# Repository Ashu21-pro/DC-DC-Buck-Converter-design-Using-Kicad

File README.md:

# Buck Converter PCB Design Using KiCad

## Overview

This project is a custom PCB design for a **DC-DC buck converter** that steps down a higher DC input voltage to a regulated **5 V output**. The design was created in KiCad, from the circuit schematic through PCB layout and 3D visualization.

The circuit uses an **LM2576HVS-5** fixed 5 V buck regulator, along with an inductor, Schottky diode, input/output capacitors, and an output indicator LED.

> **Note:** The schematic and PCB screenshots document the design process. Confirm the regulator's datasheet requirements, component ratings, footprint pin mapping, and PCB clearances before manufacturing or powering the board.

## Project Features

- Custom schematic capture in KiCad.
- Single-sided top-layer routing shown in the PCB layout.
- Screw-terminal connectors for DC input and 5 V output.
- Input and output filtering capacitors.
- Inductor and Schottky freewheeling diode for the buck-converter power stage.
- LED output indicator with a series current-limiting resistor.
- 3D PCB visualization for checking component placement and board appearance.

## Design Specifications

| Parameter | Design detail |
|---|---|
| Converter topology | Buck (step-down) DC-DC converter |
| Regulator IC | LM2576HVS-5 |
| Intended output | 5 V DC |
| Switching inductor | 100 µH (as shown in schematic) |
| Input capacitor | 100 µF (as shown in schematic) |
| Output capacitor | 100 µF (as shown in schematic) |
| Output indicator | LED with 220 Ω series resistor |
| Input connector | 2-pin screw terminal |
| Output connector | 2-pin screw terminal |
| CAD tool | KiCad |
| PCB views | Layout and 3D viewer |

**Input voltage and maximum output current:** Not specified in the screenshots. Select these from the regulator datasheet and the ratings of the diode, inductor, capacitors, connectors, and PCB traces before use.

## Circuit Operation

1. **Input supply:** DC power enters through the input screw terminal.
2. **Input filtering:** The input capacitor helps reduce supply ripple and transient disturbances.
3. **Buck conversion:** The LM2576HVS-5 switching regulator controls energy transfer through the inductor.
4. **Freewheeling path:** The Schottky diode provides a current path for the inductor when the regulator's internal switch is off.
5. **Output filtering:** The output capacitor helps smooth the converted voltage.
6. **Output connection:** The regulated output is available at the output screw terminal.
7. **Power indication:** The LED and 220 Ω resistor indicate the presence of output voltage, subject to correct polarity and wiring.

## Main Components

| Reference | Component | Value / part shown | Purpose |
|---|---|---|---|
| U1 | Buck regulator | LM2576HVS-5 | Regulates the output to 5 V |
| L1 | Inductor | 100 µH | Stores and transfers energy during switching |
| D1 | Schottky diode | Schottky type | Provides the freewheeling current path |
| C1 | Input capacitor | 100 µF | Input filtering |
| C2 | Output capacitor | 100 µF | Output filtering |
| D2 | LED | Value not specified | Output power indication |
| R1 | Resistor | 220 Ω | Limits LED current |
| J1 | 2-pin screw terminal | Input | DC input connection |
| J2 | 2-pin screw terminal | Output | 5 V output connection |

Component voltage ratings, current ratings, tolerance, ESR, package, and exact diode part number should be selected or verified against the datasheet and the intended operating conditions.

## PCB Design

The PCB layout places the regulator, inductor, diode, capacitors, indicator LED, resistor, and input/output terminals on a compact board.

Layout considerations for a switching regulator include:

- Keep high-current switching loops short and compact.
- Place the input bypass capacitor close to the regulator's input and ground pins.
- Keep the diode, regulator switch node, and inductor connections short.
- Use suitably wide copper tracks for input, output, and ground current.
- Keep the feedback connection away from noisy switching nodes and route it as recommended by the datasheet.
- Check copper clearances, thermal performance, mounting, and connector polarity before fabrication.

The screenshots show a PCB layout and a 3D preview. They are useful for reviewing placement and appearance, but they do not by themselves confirm electrical correctness or thermal suitability.

## Design Workflow

1. Draw the circuit schematic in KiCad.
2. Assign footprints to the components.
3. Transfer the components to the PCB editor.
4. Arrange components and define the board outline.
5. Route the nets and inspect track widths and clearances.
6. Run the Electrical Rules Checker (ERC) and Design Rules Checker (DRC), then resolve all relevant errors.
7. Inspect the 3D model for component orientation, footprint alignment, and connector placement.
8. Generate manufacturing files only after reviewing the schematic, layout, and component datasheets.

## Validation Checklist

Before ordering or powering the PCB:

- [ ] Verify the LM2576HVS-5 pinout against the exact package datasheet.
- [ ] Confirm that the input voltage is within the regulator's permitted range.
- [ ] Verify the Schottky diode's polarity, reverse-voltage rating, and current rating.
- [ ] Verify the inductor's saturation current, current rating, and inductance.
- [ ] Confirm capacitor polarity, voltage rating, capacitance, and required ESR.
- [ ] Check the feedback pin connection and output voltage path against the reference circuit.
- [ ] Confirm connector pin numbering and positive/ground markings.
- [ ] Run KiCad ERC and PCB DRC and resolve relevant violations.
- [ ] Inspect copper width, thermal reliefs, clearances, and component footprints.
- [ ] Perform initial power-up with a current-limited bench supply and measure the output before connecting a load.

## Repository Contents

Suggested repository structure:

```text
buck-converter/
├── README.md
├── schematic/
│   └── buck_converter.kicad_sch
├── pcb/
│   └── buck_converter.kicad_pcb
└── images/
    ├── schematic.png
    ├── pcb-layout.png
    └── pcb-3d.png
```

Update the filenames and folders to match the files actually included in the repository. Add exported screenshots to `images/` if you want them displayed in this README.

## Skills Demonstrated

- Schematic capture and PCB layout using KiCad
- Component and footprint selection
- Routing and PCB design-rule checking
- Understanding of a switching buck-converter power stage
- Connector placement, polarity marking, and 3D board inspection
- Hardware design documentation

## Disclaimer

This README describes the design shown in the project screenshots. Actual performance, output regulation, current capability, and safety have not been established by the screenshots alone. Verify the design and test it under controlled conditions before connecting it to any equipment.

## Author

**Ashutosh K. Undure**  
Electronics and Communication Engineering | Embedded Systems and PCB Design

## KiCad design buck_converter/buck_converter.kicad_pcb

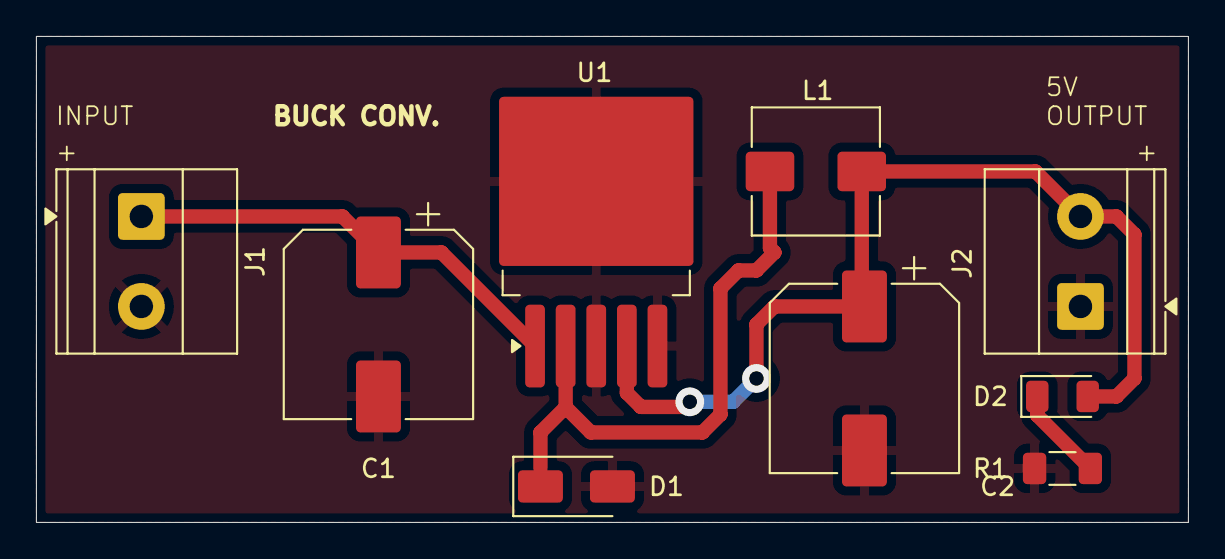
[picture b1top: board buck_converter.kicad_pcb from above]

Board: 2 copper layers, 64.0 x 27.0 mm, 9 parts (0 on the bottom side), 5 nets.

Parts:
C1, C2: 100uF; CP_Elec_10x10
D1: D_Schottky; D_SMA
D2: LED; LED_1206_3216Metric
J1, J2: Screw_Terminal_01x02; TerminalBlock_Phoenix_MKDS-1,5-2_1x02_P5.00mm_Horizontal
L1: 100uH; L_Wuerth_HCI-7040
R1: 220R; R_1206_3216Metric_Pad1.30x1.75mm_HandSolder
U1: LM2576HVS-5; TO-263-5_TabPin3

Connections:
GND: C1.2, C2.2, D1.2 (A), J1.2, J2.1, R1.2, U1.3 (GND), U1.5 (~ON/OFF)
unnamed: D1.1 (K), L1.1, U1.2 (OUT)
unnamed: C2.1, D2.2 (A), J2.2, L1.2, U1.4 (FB)
unnamed: D2.1 (K), R1.1
unnamed: C1.1, J1.1, U1.1 (VIN)
